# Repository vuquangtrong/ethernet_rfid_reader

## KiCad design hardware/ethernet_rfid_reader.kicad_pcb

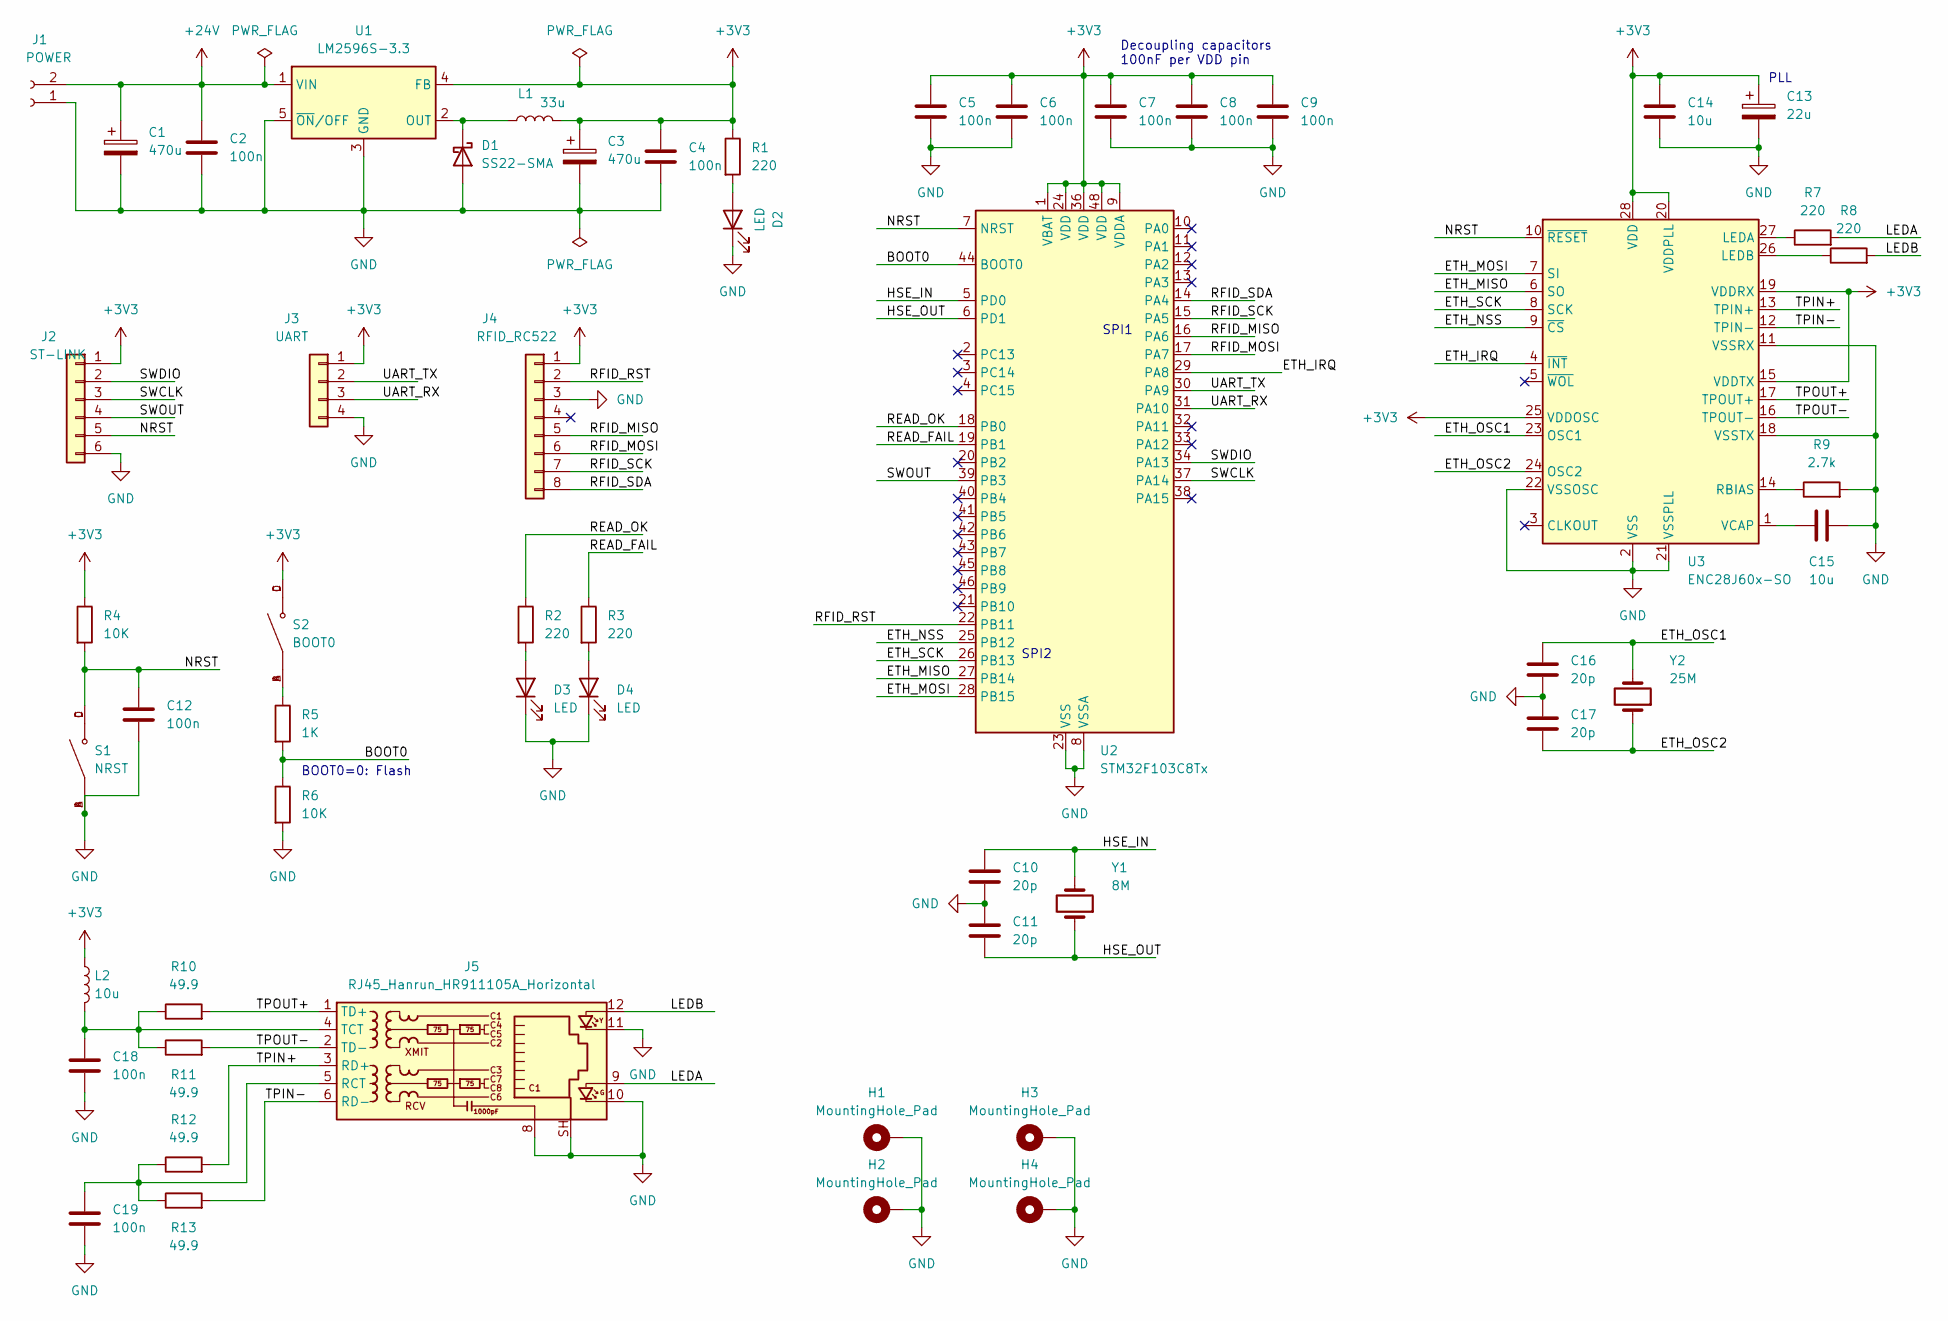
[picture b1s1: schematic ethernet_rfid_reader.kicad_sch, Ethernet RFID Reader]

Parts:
C1, C3: 470u; CP_Elec_8x10
C2, C4, C5, C6, C7, C8, C9, C12, C18, C19: 100n; C_0805_2012Metric
C10, C11, C16, C17: 20p; C_0603_1608Metric
C13: 22u; C_0805_2012Metric
C14, C15: 10u; C_0603_1608Metric
D1: SS22-SMA; D_SMA
D2, D3, D4: LED; LED_D3.0mm_Horizontal_O1.27mm_Z2.0mm
H1, H2, H3, H4: MountingHole_Pad; MountingHole_3.5mm_Pad
J1: POWER; JST_XH_S2B-XH-A_1x02_P2.50mm_Horizontal
J2: ST-LINK; PinHeader_1x06_P2.54mm_Vertical
J3: UART; PinHeader_1x04_P2.54mm_Vertical
J4: RFID_RC522; MODULE_CEG006900_1
J5: RJ45_Hanrun_HR911105A_Horizontal
L1: 33u; L_7.3x7.3_H4.5
L2: 10u; L_1206_3216Metric
R1, R2, R3, R7, R8: 220; R_0805_2012Metric
R4, R6: 10K; R_0805_2012Metric
R5: 1K; R_0805_2012Metric
R9: 2.7k; R_0805_2012Metric
R10, R11, R12, R13: 49.9; R_0805_2012Metric
S1: NRST; SW_TS-1187A-B-A-B
S2: BOOT0; SW_TS-1187A-B-A-B
U1: LM2596S-3.3; TO-263-5_TabPin3
U2: STM32F103C8Tx; LQFP-48_7x7mm_P0.5mm
U3: ENC28J60x-SO; SOIC-28W_7.5x17.9mm_P1.27mm
Y1: 8M; Crystal_SMD_HC49-SD
Y2: 25M; Crystal_SMD_HC49-SD

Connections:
+3V3: C3.1, C4.1, C5.1, C6.1, C7.1, C8.1, C9.1, C13.1, C14.1, J2.1, J3.1, J4.1, L1.2, L2.1, R1.1, R4.1, S2.C, S2.D, U1.4 (FB), U2.1 (VBAT), U2.9 (VDDA), U2.24 (VDD), U2.36 (VDD), U2.48 (VDD), U3.15 (VDDTX), U3.19 (VDDRX), U3.20 (VDDPLL), U3.25 (VDDOSC), U3.28 (VDD)
+24V: C1.1, C2.1, J1.2, U1.1 (VIN)
/BOOT0: R5.2, R6.1, U2.44 (BOOT0)
/ETH_IRQ: U2.29 (PA8), U3.4 (~INT)
/ETH_MISO: U2.27 (PB14), U3.6 (SO)
/ETH_MOSI: U2.28 (PB15), U3.7 (SI)
/ETH_NSS: U2.25 (PB12), U3.9 (~CS)
/ETH_OSC1: C16.1, U3.23 (OSC1), Y2.2
/ETH_OSC2: C17.2, U3.24 (OSC2), Y2.1
/ETH_SCK: U2.26 (PB13), U3.8 (SCK)
/HSE_IN: C10.1, U2.5 (PD0), Y1.2
/HSE_OUT: C11.2, U2.6 (PD1), Y1.1
/LEDA: J5.9, R7.2
/LEDB: J5.12, R8.2
/NRST: C12.2, J2.5, R4.2, S1.C, S1.D, U2.7 (NRST), U3.10 (~RESET)
/READ_FAIL: R3.1, U2.19 (PB1)
/READ_OK: R2.1, U2.18 (PB0)
/RFID_MISO: J4.5, U2.16 (PA6)
/RFID_MOSI: J4.6, U2.17 (PA7)
/RFID_RST: J4.2, U2.22 (PB11)
/RFID_SCK: J4.7, U2.15 (PA5)
/RFID_SDA: J4.8, U2.14 (PA4)
/SWCLK: J2.3, U2.37 (PA14)
/SWDIO: J2.2, U2.34 (PA13)
/SWOUT: J2.4, U2.39 (PB3)
/TPIN+: J5.3 (RD+), R12.2, U3.13 (TPIN+)
/TPIN-: J5.6 (RD-), R13.2, U3.12 (TPIN-)
/TPOUT+: J5.1 (TD+), R10.2, U3.17 (TPOUT+)
/TPOUT-: J5.2 (TD-), R11.2, U3.16 (TPOUT-)
/UART_RX: J3.3, U2.31 (PA10)
/UART_TX: J3.2, U2.30 (PA9)
GND: C1.2, C2.2, C3.2, C4.2, C5.2, C6.2, C7.2, C8.2, C9.2, C10.2, C11.1, C12.1, C13.2, C14.2, C15.2, C16.2, C17.1, C18.2, C19.2, D1.2 (A), D2.1 (K), D3.1 (K), D4.1 (K), H1.1, H2.1, H3.1, H4.1, J1.1, J2.6, J3.4, J4.3, J5.8, J5.10, J5.11, J5.SH, R6.2, R9.2, S1.A, S1.B, U1.3 (GND), U1.5 (~ON/OFF), U2.8 (VSSA), U2.23 (VSS), U2.35 (VSS), U2.47 (VSS), U3.2 (VSS), U3.11 (VSSRX), U3.18 (VSSTX), U3.21 (VSSPLL), U3.22 (VSSOSC)
unnamed: D1.1 (K), L1.1, U1.2 (OUT)
unnamed: D2.2 (A), R1.2
unnamed: D3.2 (A), R2.2
unnamed: D4.2 (A), R3.2
unnamed: C19.1, J5.5 (RCT), R12.1, R13.1
unnamed: C18.1, J5.4 (TCT), L2.2, R10.1, R11.1
unnamed: R5.1, S2.A, S2.B
unnamed: R7.1, U3.27 (LEDA)
unnamed: R8.1, U3.26 (LEDB)
unnamed: R9.1, U3.14 (RBIAS)
unnamed: C15.1, U3.1 (VCAP)

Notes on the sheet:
PLL
Decoupling capacitors 100nF per VDD pin
SPI2
SPI1
BOOT0=0: Flash

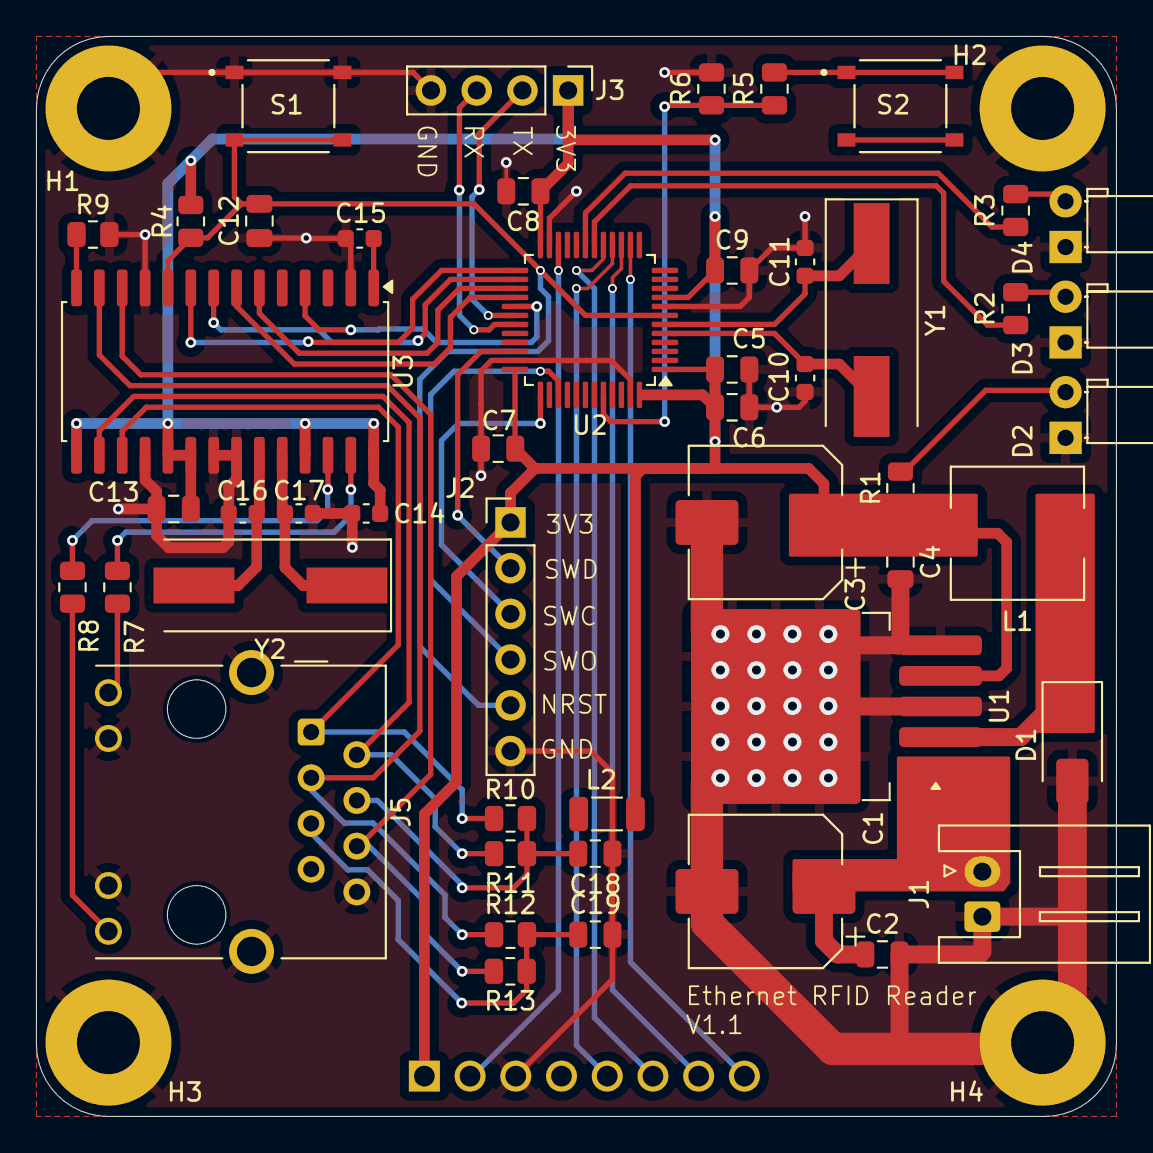
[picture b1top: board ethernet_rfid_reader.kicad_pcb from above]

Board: 2 copper layers, 60.0 x 60.0 mm, 54 parts (1 on the bottom side), 43 nets.

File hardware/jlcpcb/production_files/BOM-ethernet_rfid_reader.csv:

Comment,Designator,Footprint,LCSC,Quantity
10u,L2,L_1206_3216Metric,C1046,1
RJ45_Hanrun_HR911105A_Horizontal,J5,RJ45_Hanrun_HR911105A_Horizontal,C12074,1
8M,Y1,Crystal_SMD_HC49-SD,C12674,1
25M,Y2,Crystal_SMD_HC49-SD,C14872,1
POWER,J1,JST_XH_S2B-XH-A_1x02_P2.50mm_Horizontal,C158012,1
20p,"C10,C11,C16,C17",C_0603_1608Metric,C1648,4
10K,"R4,R6",R_0805_2012Metric,C17414,2
1K,R5,R_0805_2012Metric,C17513,1
2.7k,R9,R_0805_2012Metric,C17530,1
220,"R1,R2,R3,R7,R8",R_0805_2012Metric,C17557,5
49.9,"R10,R11,R12,R13",R_0805_2012Metric,C17720,4
10u,"C14,C15",C_0603_1608Metric,C19702,2
SS22-SMA,D1,D_SMA,C2891712,1
NRST,"S1,S2",SW_TS-1187A-B-A-B,C318884,2
22u,C13,C_0805_2012Metric,C45783,1
ENC28J60x-SO,U3,SOIC-28W_7.5x17.9mm_P1.27mm,C47351,1
100n,"C12,C18,C19,C2,C4,C5,C6,C7,C8,C9",C_0805_2012Metric,C49678,10
LM2596S-3.3,U1,TO-263-5_TabPin3,C5189812,1
33u,L1,L_7.3x7.3_H4.5,C5339524,1
470u,"C1,C3",CP_Elec_8x10,C7471889,2
STM32F103C8Tx,U2,LQFP-48_7x7mm_P0.5mm,C8734,1

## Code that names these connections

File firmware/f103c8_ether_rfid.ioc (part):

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Mcu.Name=STM32F103C(8-B)Tx
Mcu.Package=LQFP48
Mcu.UserName=STM32F103C8Tx
PA10.Mode=Asynchronous
PA10.Signal=USART1_RX
PA13.Mode=Serial_Wire
PA13.Signal=SYS_JTMS-SWDIO
PA14.Mode=Serial_Wire
PA14.Signal=SYS_JTCK-SWCLK
PA4.GPIOParameters=GPIO_Speed,GPIO_Label
PA4.GPIO_Label=RFID_SDA
PA4.GPIO_Speed=GPIO_SPEED_FREQ_HIGH
PA4.Signal=GPIO_Output
PA5.GPIOParameters=GPIO_Label
PA5.GPIO_Label=RFID_SCK
PA5.Mode=Full_Duplex_Master
PA5.Signal=SPI1_SCK
PA6.GPIOParameters=GPIO_Label
PA6.GPIO_Label=RFID_MISO
PA6.Mode=Full_Duplex_Master
PA6.Signal=SPI1_MISO
PA7.GPIOParameters=GPIO_Label
PA7.GPIO_Label=RFID_MOSI
PA7.Mode=Full_Duplex_Master
PA7.Signal=SPI1_MOSI
PA8.GPIOParameters=GPIO_Label,GPIO_ModeDefaultEXTI
PA8.GPIO_Label=ETH_IRQ
PA8.GPIO_ModeDefaultEXTI=GPIO_MODE_IT_FALLING
PA8.Signal=GPXTI8
PA9.Mode=Asynchronous
PA9.Signal=USART1_TX
PB0.GPIOParameters=GPIO_Label
PB0.GPIO_Label=READ_OK
PB0.Signal=GPIO_Output
PB1.GPIOParameters=GPIO_Label
PB1.GPIO_Label=READ_FAIL
PB1.Signal=GPIO_Output
PB11.GPIOParameters=GPIO_Speed,GPIO_Label
PB11.GPIO_Label=RFID_RST
PB11.GPIO_Speed=GPIO_SPEED_FREQ_HIGH
PB11.Signal=GPIO_Output
PB12.GPIOParameters=GPIO_Speed,GPIO_Label
PB12.GPIO_Label=ETH_NSS
PB12.GPIO_Speed=GPIO_SPEED_FREQ_HIGH
PB12.Signal=GPIO_Output
PB13.GPIOParameters=GPIO_Label
PB13.GPIO_Label=ETH_SCK
PB13.Mode=Full_Duplex_Master
PB13.Signal=SPI2_SCK
PB14.GPIOParameters=GPIO_Label
PB14.GPIO_Label=ETH_MISO
PB14.Mode=Full_Duplex_Master
PB14.Signal=SPI2_MISO
PB15.GPIOParameters=GPIO_Label
PB15.GPIO_Label=ETH_MOSI
PB15.Mode=Full_Duplex_Master
PB15.Signal=SPI2_MOSI
PD0-OSC_IN.Mode=HSE-External-Oscillator
PD0-OSC_IN.Signal=RCC_OSC_IN
PD1-OSC_OUT.Mode=HSE-External-Oscillator
PD1-OSC_OUT.Signal=RCC_OSC_OUT
RCC.SYSCLKFreq_VALUE=72000000
RCC.SYSCLKSource=RCC_SYSCLKSOURCE_PLLCLK
board=custom

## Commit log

2024-11-09 Init project, hardware v1.0
2024-11-30 Init firmware
2024-11-30 Add App module
2024-12-01 Add ENC28J60 driver
2024-12-02 Add LwIP module
2024-12-06 Update App structure to call LwIP
2024-12-06 Implement Ethernet Interface. Can send ARP and PING (ICMP)
2024-12-07 Update LwIP Options
